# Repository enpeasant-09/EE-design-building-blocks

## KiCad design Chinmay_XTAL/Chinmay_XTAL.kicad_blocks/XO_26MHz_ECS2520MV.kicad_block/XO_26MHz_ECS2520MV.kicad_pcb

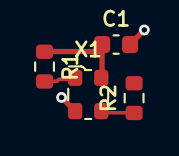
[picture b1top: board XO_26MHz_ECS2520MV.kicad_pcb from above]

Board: 2 copper layers, 4 parts (0 on the bottom side), 4 nets.

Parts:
C1: 100nF; C_0603_1608Metric
R1: 10k; R_0603_1608Metric
R2: 27R; R_0603_1608Metric
X1: 26MHz; Oscillator_SMD_ECS_2520MV-xxx-xx-4Pin_2.5x2.0mm

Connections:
GND: C1.2, X1.2
unnamed: R2.1, X1.3
OE: R1.2, X1.1
VDD: C1.1, R1.1, X1.4
